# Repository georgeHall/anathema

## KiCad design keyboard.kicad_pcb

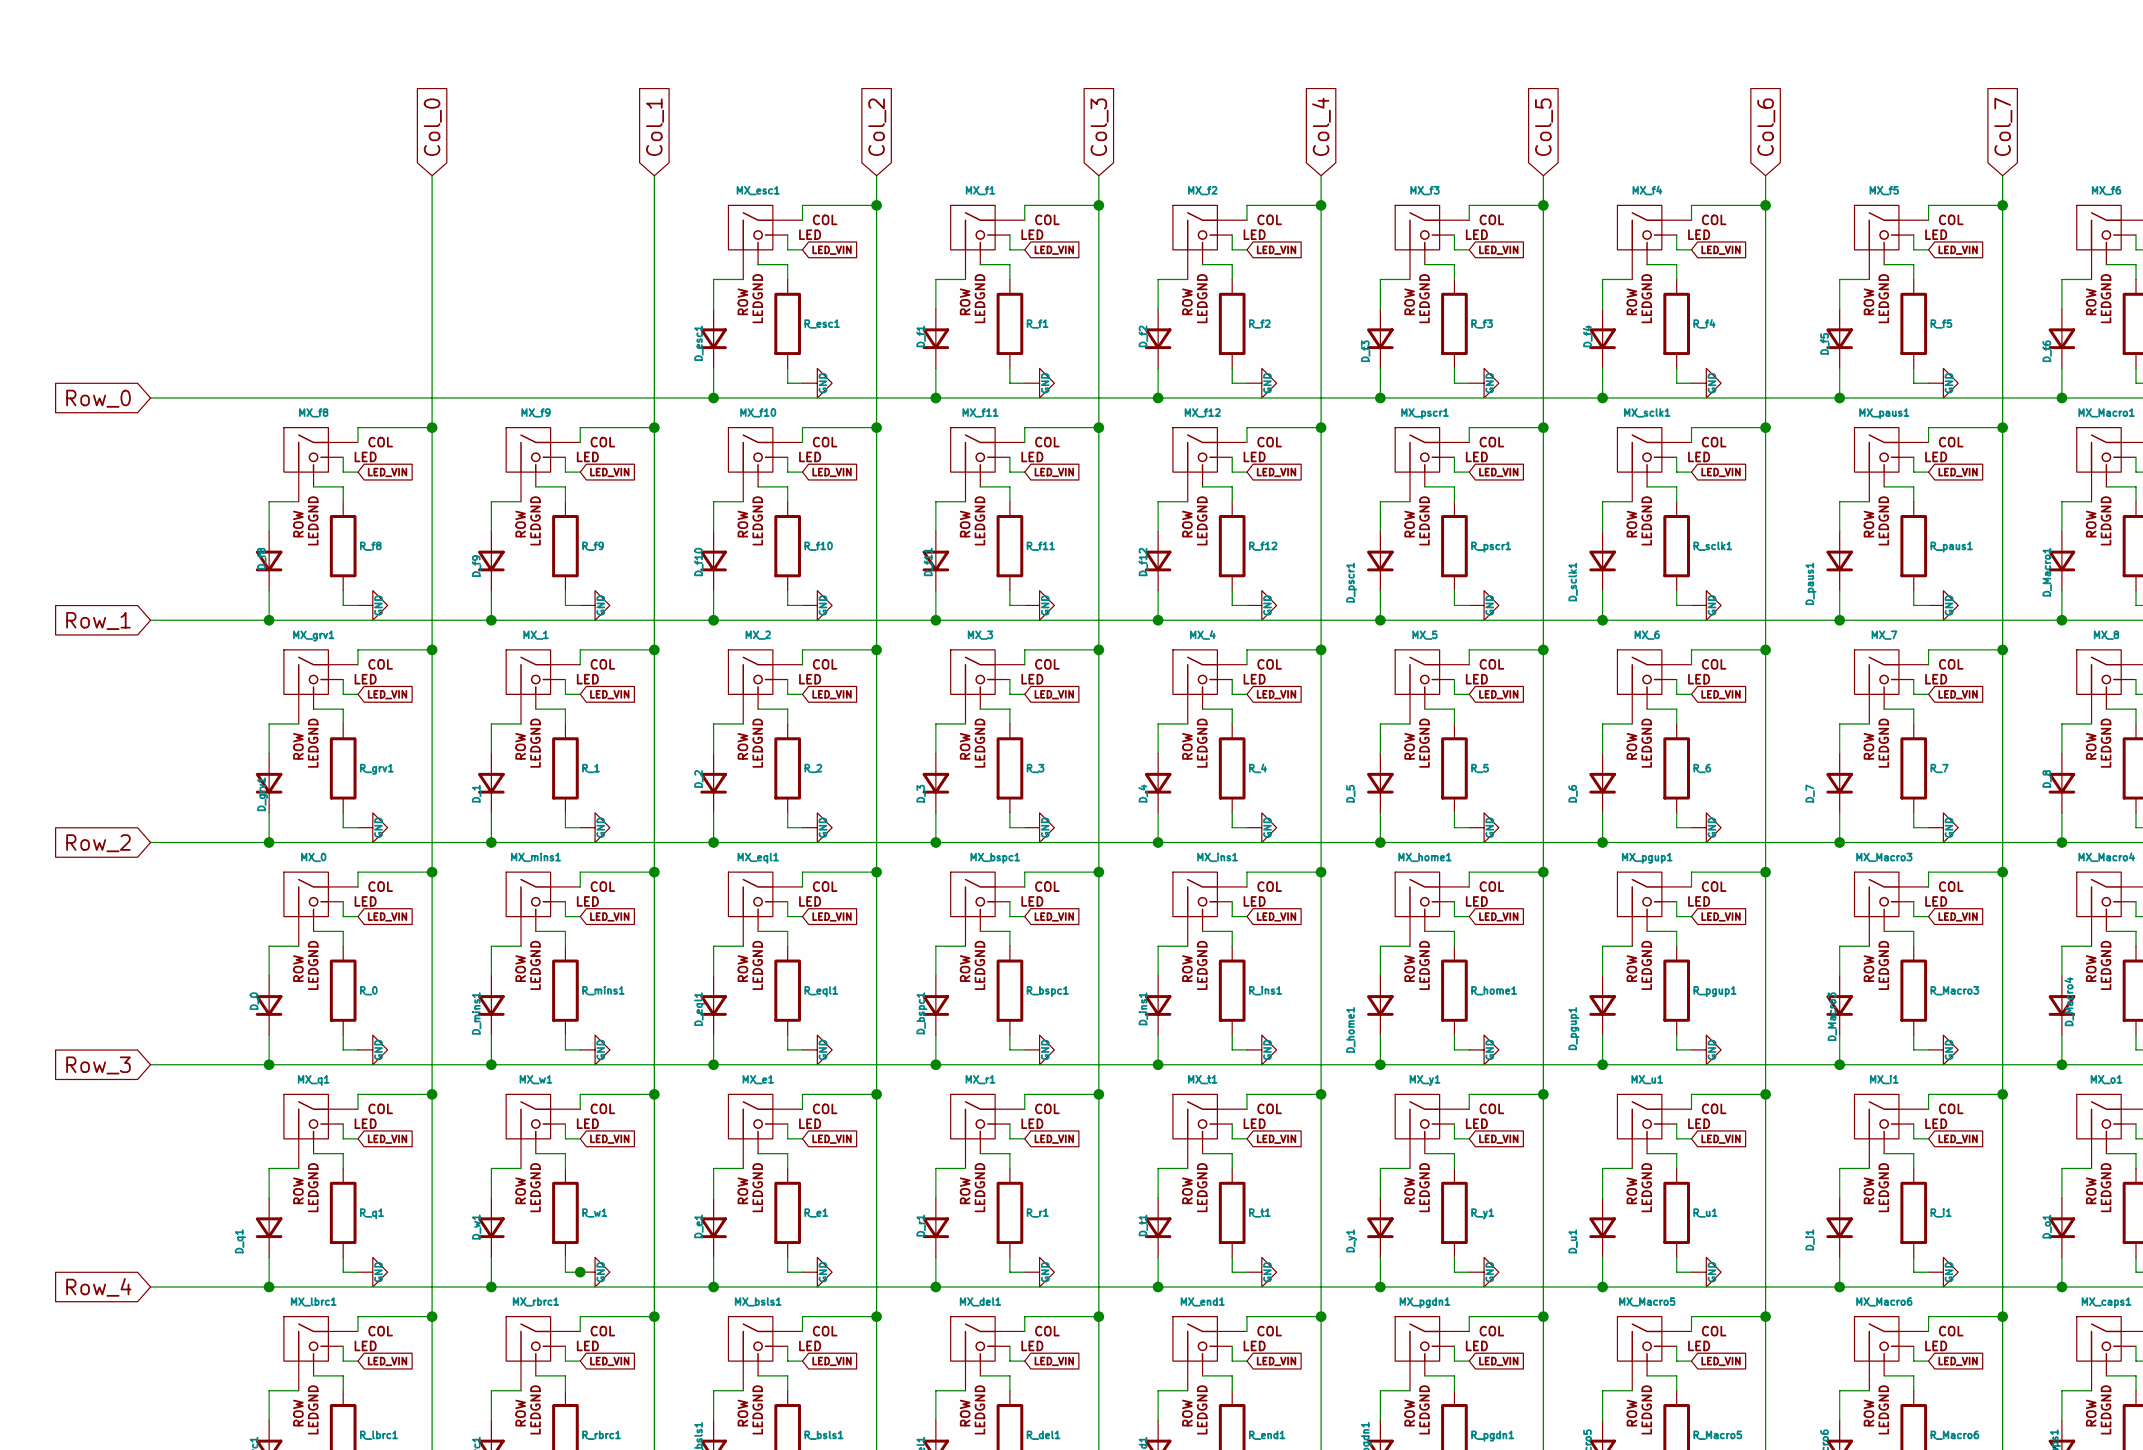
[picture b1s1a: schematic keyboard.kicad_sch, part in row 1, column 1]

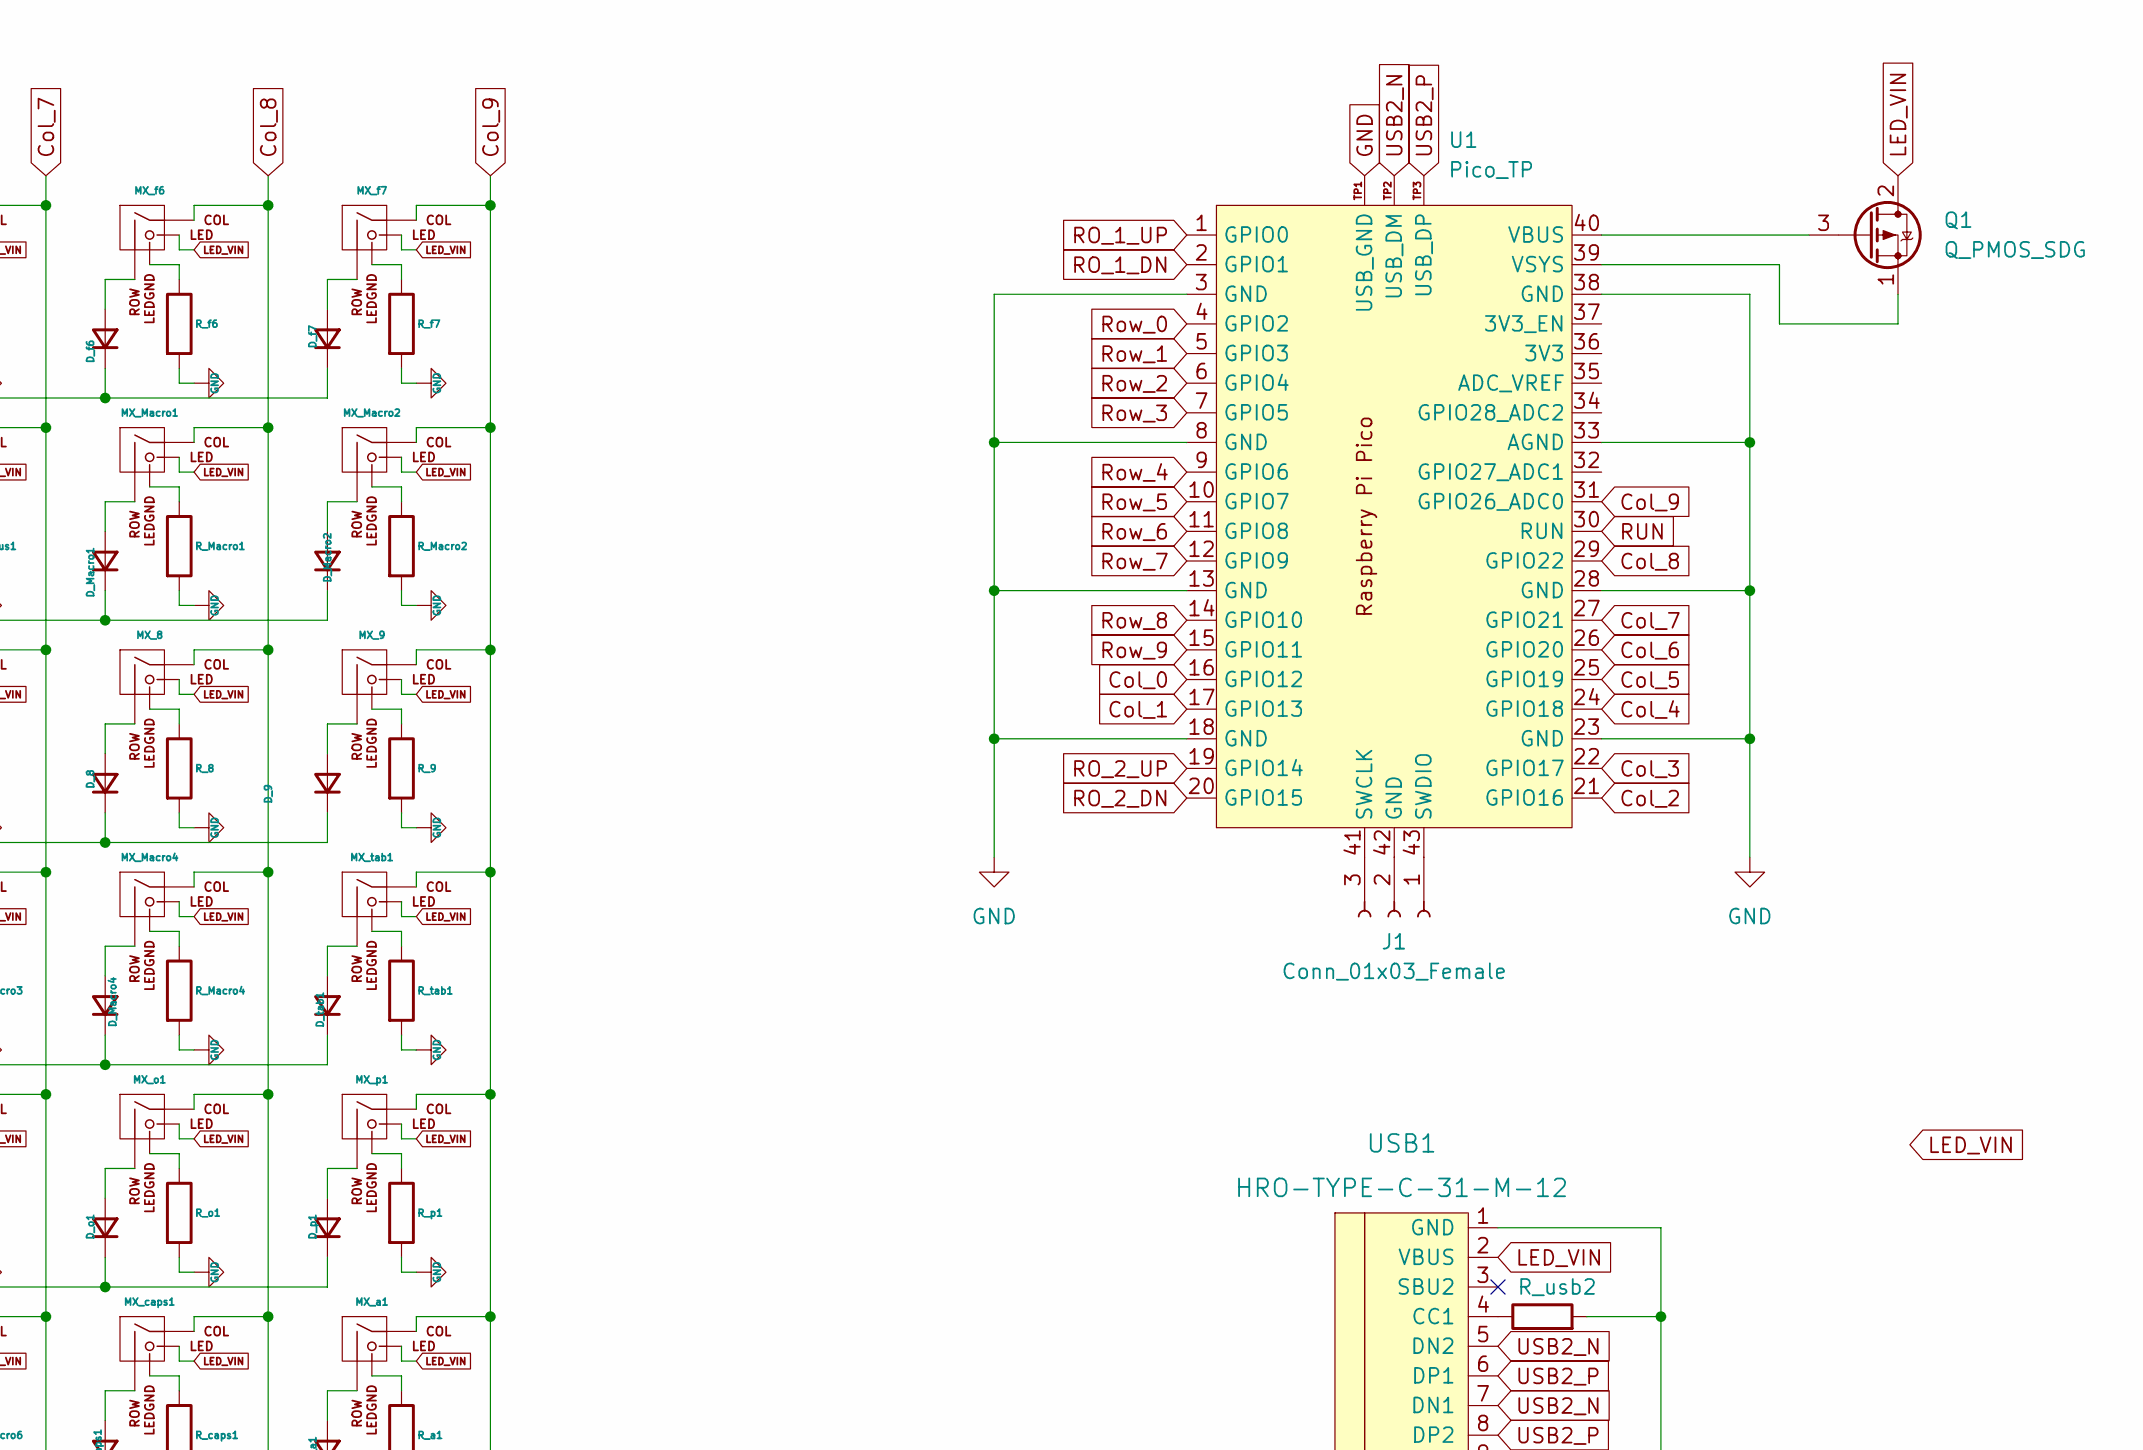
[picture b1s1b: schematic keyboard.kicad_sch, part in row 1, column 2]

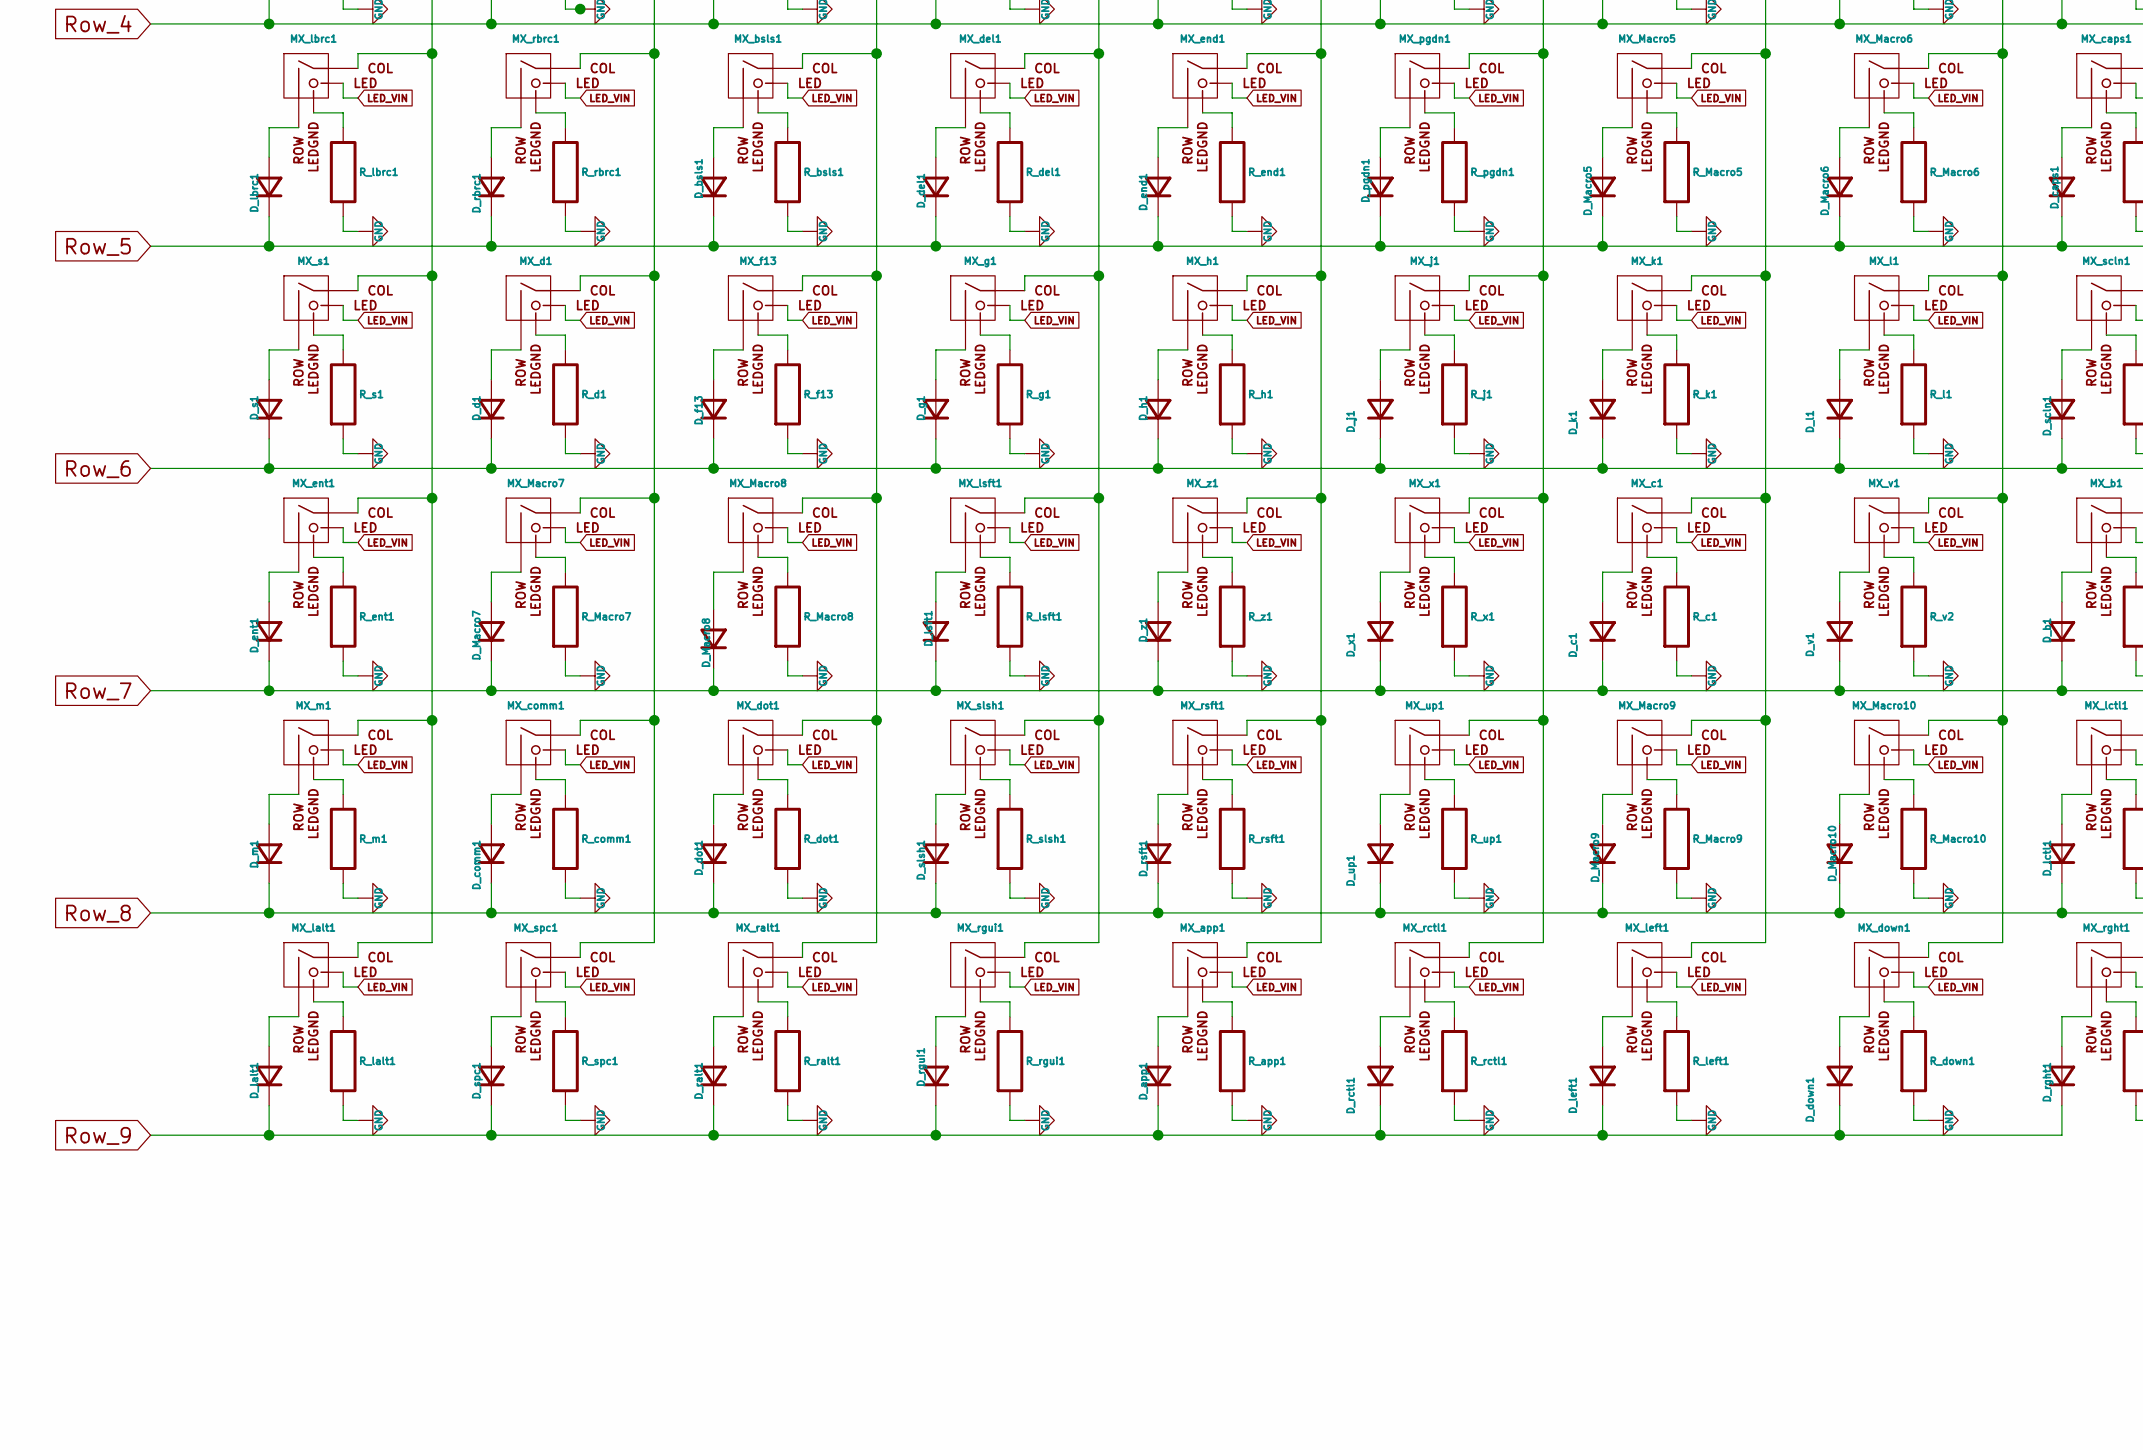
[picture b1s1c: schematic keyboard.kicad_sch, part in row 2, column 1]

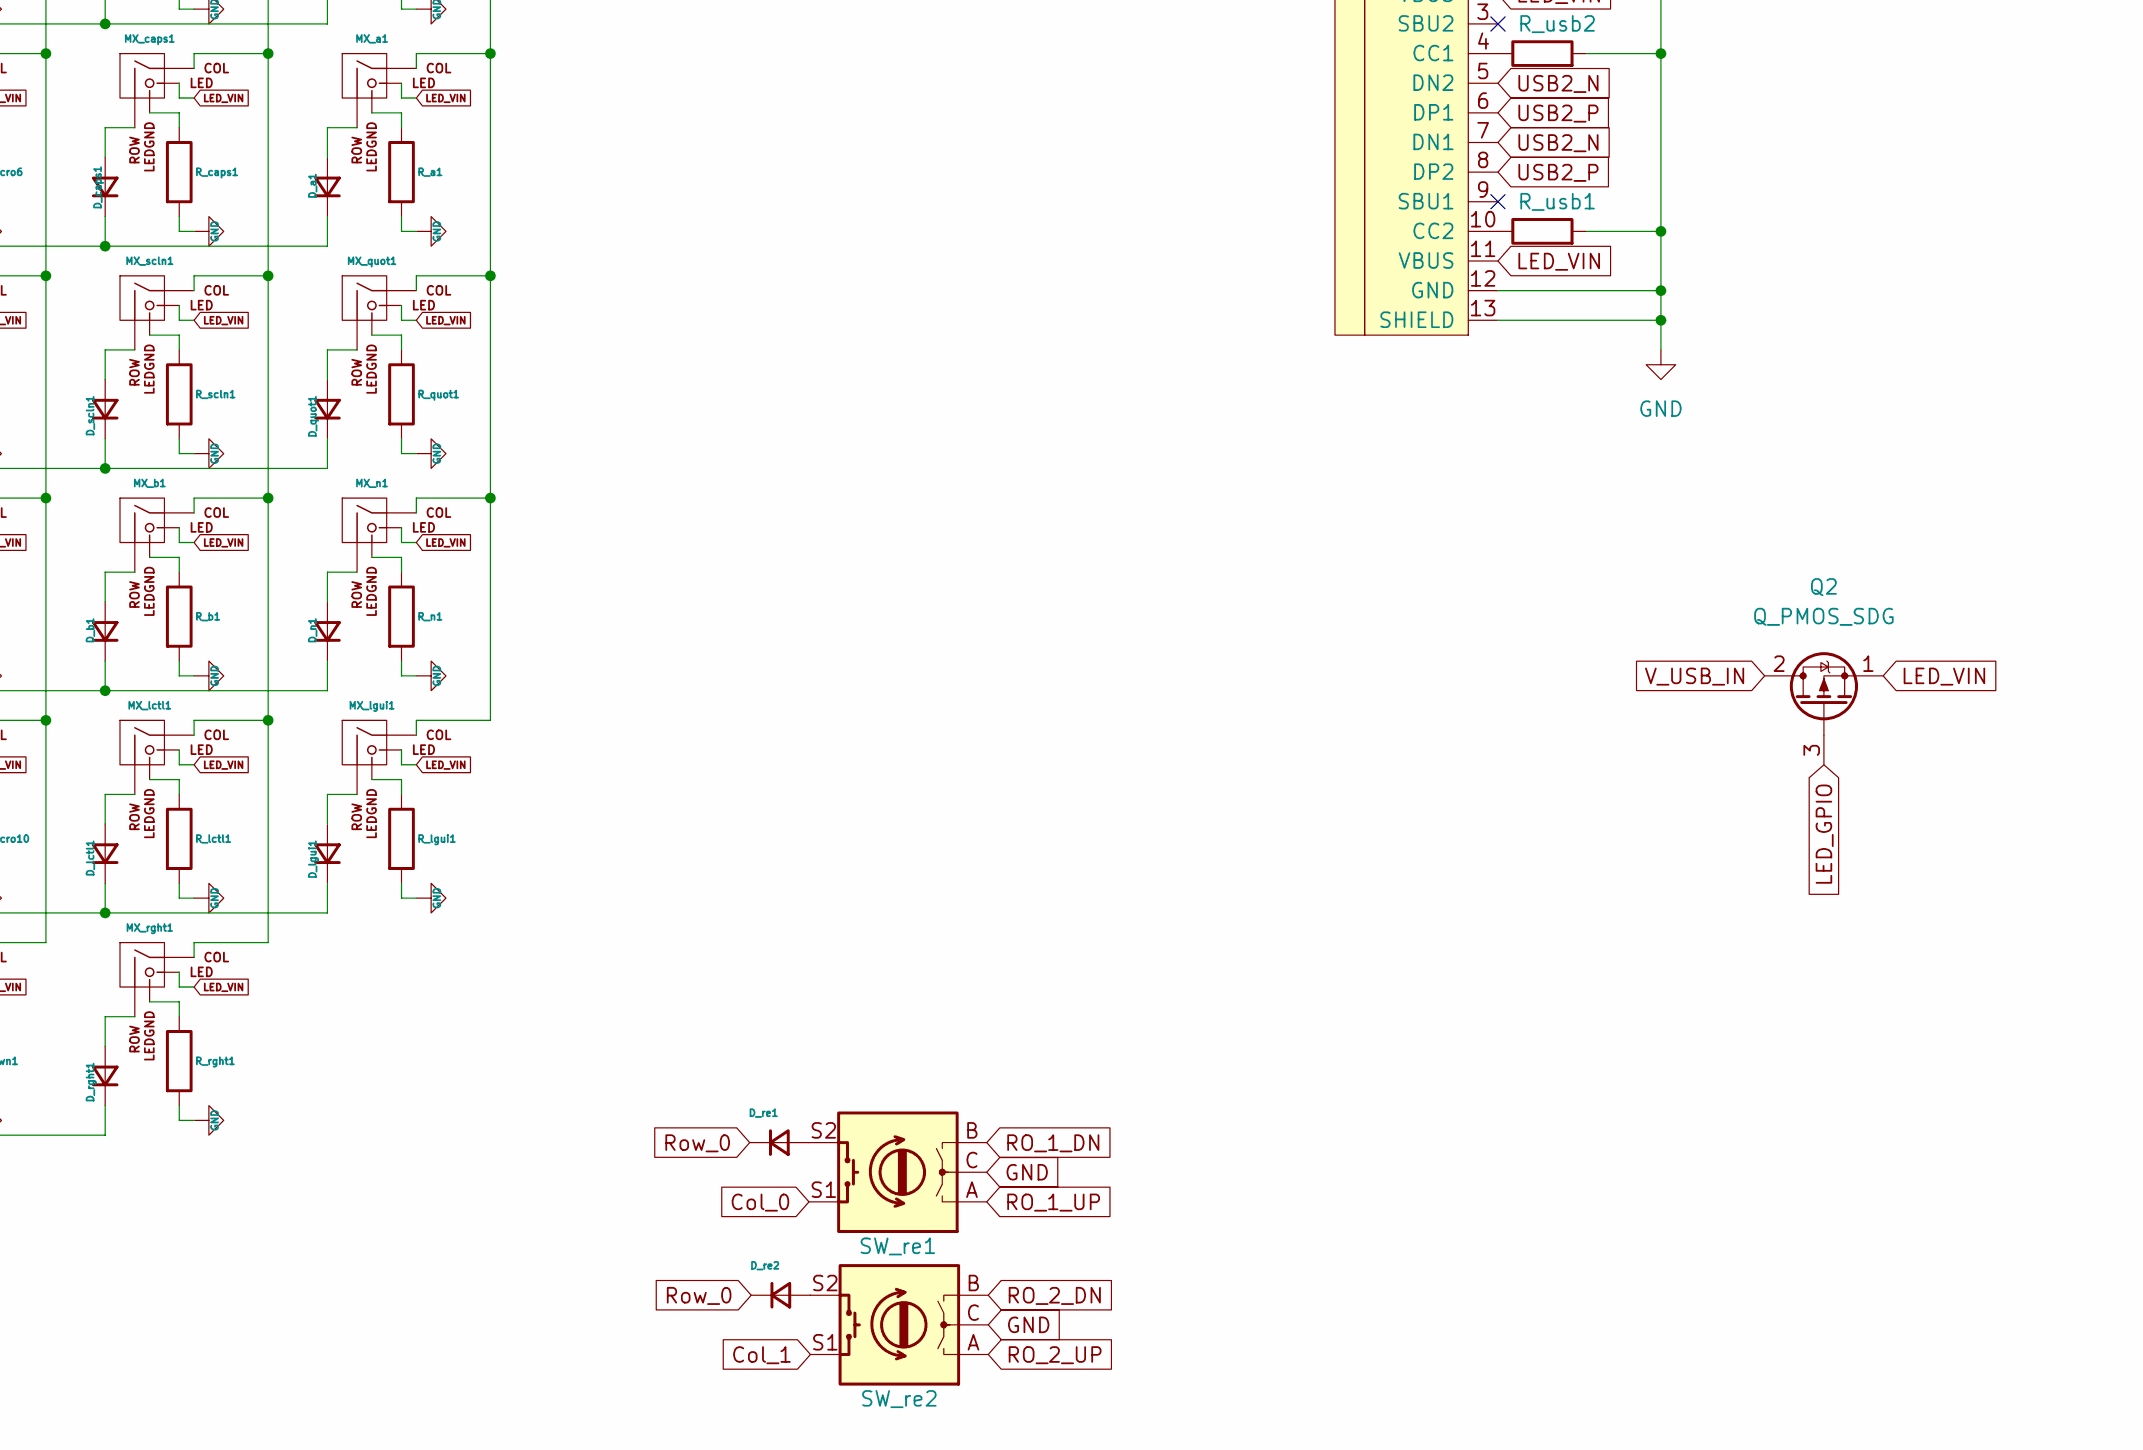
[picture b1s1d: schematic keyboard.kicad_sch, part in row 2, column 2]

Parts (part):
D_0, D_1, D_2, D_3, D_4, D_5, D_6, D_7, D_8, D_9: D_Small; D_0805_2012Metric_Pad1.15x1.40mm_HandSolder
D_Macro1, D_Macro2, D_Macro3, D_Macro4, D_Macro5, D_Macro6, D_Macro7, D_Macro8, D_Macro9, D_Macro10: D_Small; D_0805_2012Metric_Pad1.15x1.40mm_HandSolder
D_a1: D_Small; D_0805_2012Metric_Pad1.15x1.40mm_HandSolder
D_app1: D_Small; D_0805_2012Metric_Pad1.15x1.40mm_HandSolder
D_b1: D_Small; D_0805_2012Metric_Pad1.15x1.40mm_HandSolder
D_bsls1: D_Small; D_0805_2012Metric_Pad1.15x1.40mm_HandSolder
D_bspc1: D_Small; D_0805_2012Metric_Pad1.15x1.40mm_HandSolder
D_c1: D_Small; D_0805_2012Metric_Pad1.15x1.40mm_HandSolder
D_caps1: D_Small; D_0805_2012Metric_Pad1.15x1.40mm_HandSolder
D_comm1: D_Small; D_0805_2012Metric_Pad1.15x1.40mm_HandSolder
D_d1: D_Small; D_0805_2012Metric_Pad1.15x1.40mm_HandSolder
D_del1: D_Small; D_0805_2012Metric_Pad1.15x1.40mm_HandSolder
D_dot1: D_Small; D_0805_2012Metric_Pad1.15x1.40mm_HandSolder
D_down1: D_Small; D_0805_2012Metric_Pad1.15x1.40mm_HandSolder
D_e1: D_Small; D_0805_2012Metric_Pad1.15x1.40mm_HandSolder
D_end1: D_Small; D_0805_2012Metric_Pad1.15x1.40mm_HandSolder
D_ent1: D_Small; D_0805_2012Metric_Pad1.15x1.40mm_HandSolder
D_eql1: D_Small; D_0805_2012Metric_Pad1.15x1.40mm_HandSolder
D_esc1: D_Small; D_0805_2012Metric_Pad1.15x1.40mm_HandSolder
D_f1, D_f2, D_f3, D_f4, D_f5, D_f6, D_f7, D_f8, D_f9, D_f10, D_f11, D_f12, D_f13: D_Small; D_0805_2012Metric_Pad1.15x1.40mm_HandSolder
D_g1: D_Small; D_0805_2012Metric_Pad1.15x1.40mm_HandSolder
D_grv1: D_Small; D_0805_2012Metric_Pad1.15x1.40mm_HandSolder
D_h1: D_Small; D_0805_2012Metric_Pad1.15x1.40mm_HandSolder
D_home1: D_Small; D_0805_2012Metric_Pad1.15x1.40mm_HandSolder
D_i1: D_Small; D_0805_2012Metric_Pad1.15x1.40mm_HandSolder
D_ins1: D_Small; D_0805_2012Metric_Pad1.15x1.40mm_HandSolder
D_j1: D_Small; D_0805_2012Metric_Pad1.15x1.40mm_HandSolder
D_k1: D_Small; D_0805_2012Metric_Pad1.15x1.40mm_HandSolder
D_l1: D_Small; D_0805_2012Metric_Pad1.15x1.40mm_HandSolder
D_lalt1: D_Small; D_0805_2012Metric_Pad1.15x1.40mm_HandSolder
D_lbrc1: D_Small; D_0805_2012Metric_Pad1.15x1.40mm_HandSolder
D_lctl1: D_Small; D_0805_2012Metric_Pad1.15x1.40mm_HandSolder
D_left1: D_Small; D_0805_2012Metric_Pad1.15x1.40mm_HandSolder
D_lgui1: D_Small; D_0805_2012Metric_Pad1.15x1.40mm_HandSolder
D_lsft1: D_Small; D_0805_2012Metric_Pad1.15x1.40mm_HandSolder
D_m1: D_Small; D_0805_2012Metric_Pad1.15x1.40mm_HandSolder
D_mins1: D_Small; D_0805_2012Metric_Pad1.15x1.40mm_HandSolder
D_n1: D_Small; D_0805_2012Metric_Pad1.15x1.40mm_HandSolder
D_o1: D_Small; D_0805_2012Metric_Pad1.15x1.40mm_HandSolder
D_p1: D_Small; D_0805_2012Metric_Pad1.15x1.40mm_HandSolder
D_paus1: D_Small; D_0805_2012Metric_Pad1.15x1.40mm_HandSolder
D_pgdn1: D_Small; D_0805_2012Metric_Pad1.15x1.40mm_HandSolder
D_pgup1: D_Small; D_0805_2012Metric_Pad1.15x1.40mm_HandSolder
D_pscr1: D_Small; D_0805_2012Metric_Pad1.15x1.40mm_HandSolder
D_q1: D_Small; D_0805_2012Metric_Pad1.15x1.40mm_HandSolder
D_quot1: D_Small; D_0805_2012Metric_Pad1.15x1.40mm_HandSolder
D_r1: D_Small; D_0805_2012Metric_Pad1.15x1.40mm_HandSolder
D_ralt1: D_Small; D_0805_2012Metric_Pad1.15x1.40mm_HandSolder
D_rbrc1: D_Small; D_0805_2012Metric_Pad1.15x1.40mm_HandSolder
D_rctl1: D_Small; D_0805_2012Metric_Pad1.15x1.40mm_HandSolder
D_re1, D_re2: D_Small; D_0805_2012Metric_Pad1.15x1.40mm_HandSolder
D_rght1: D_Small; D_0805_2012Metric_Pad1.15x1.40mm_HandSolder
D_rgui1: D_Small; D_0805_2012Metric_Pad1.15x1.40mm_HandSolder
D_rsft1: D_Small; D_0805_2012Metric_Pad1.15x1.40mm_HandSolder
D_s1: D_Small; D_0805_2012Metric_Pad1.15x1.40mm_HandSolder
D_sclk1: D_Small; D_0805_2012Metric_Pad1.15x1.40mm_HandSolder
D_scln1: D_Small; D_0805_2012Metric_Pad1.15x1.40mm_HandSolder
D_slsh1: D_Small; D_0805_2012Metric_Pad1.15x1.40mm_HandSolder
D_spc1: D_Small; D_0805_2012Metric_Pad1.15x1.40mm_HandSolder
D_t1: D_Small; D_0805_2012Metric_Pad1.15x1.40mm_HandSolder
D_tab1: D_Small; D_0805_2012Metric_Pad1.15x1.40mm_HandSolder
D_u1: D_Small; D_0805_2012Metric_Pad1.15x1.40mm_HandSolder
D_up1: D_Small; D_0805_2012Metric_Pad1.15x1.40mm_HandSolder
D_v1: D_Small; D_0805_2012Metric_Pad1.15x1.40mm_HandSolder
D_w1: D_Small; D_0805_2012Metric_Pad1.15x1.40mm_HandSolder
D_x1: D_Small; D_0805_2012Metric_Pad1.15x1.40mm_HandSolder
D_y1: D_Small; D_0805_2012Metric_Pad1.15x1.40mm_HandSolder
D_z1: D_Small; D_0805_2012Metric_Pad1.15x1.40mm_HandSolder
J1: Conn_01x03_Female
MX_0, MX_1, MX_2, MX_3, MX_4, MX_5, MX_6, MX_7, MX_8, MX_9: MX-LED; MXOnly-1U
MX_Macro1, MX_Macro2, MX_Macro3, MX_Macro4, MX_Macro5, MX_Macro6, MX_Macro7, MX_Macro8, MX_Macro9, MX_Macro10: MX-LED; MXOnly-1U
MX_a1: MX-LED; MXOnly-1U
MX_app1: MX-LED; MXOnly-1.25U
MX_b1: MX-LED; MXOnly-1U
MX_bsls1: MX-LED; MXOnly-1.5U
MX_bspc1: MX-LED; MXOnly-2U
MX_c1: MX-LED; MXOnly-1U
MX_caps1: MX-LED; MXOnly-1.75U
MX_comm1: MX-LED; MXOnly-1U
MX_d1: MX-LED; MXOnly-1U
MX_del1: MX-LED; MXOnly-1U
MX_dot1: MX-LED; MXOnly-1U
MX_down1: MX-LED; MXOnly-1U
MX_e1: MX-LED; MXOnly-1U
MX_end1: MX-LED; MXOnly-1U
MX_ent1: MX-LED; MXOnly-2.25U
MX_eql1: MX-LED; MXOnly-1U
MX_esc1: MX-LED; MXOnly-1U
MX_f1, MX_f2, MX_f3, MX_f4, MX_f5, MX_f6, MX_f7, MX_f8, MX_f9, MX_f10, MX_f11, MX_f12, MX_f13: MX-LED; MXOnly-1U
MX_g1: MX-LED; MXOnly-1U
MX_grv1: MX-LED; MXOnly-1U
MX_h1: MX-LED; MXOnly-1U
MX_home1: MX-LED; MXOnly-1U
MX_i1: MX-LED; MXOnly-1U
MX_ins1: MX-LED; MXOnly-1U
MX_j1: MX-LED; MXOnly-1U
MX_k1: MX-LED; MXOnly-1U
MX_l1: MX-LED; MXOnly-1U
MX_lalt1: MX-LED; MXOnly-1.25U
MX_lbrc1: MX-LED; MXOnly-1U
MX_lctl1: MX-LED; MXOnly-1.25U
MX_left1: MX-LED; MXOnly-1U
MX_lgui1: MX-LED; MXOnly-1.25U
MX_lsft1: MX-LED; MXOnly-2.25U
MX_m1: MX-LED; MXOnly-1U
MX_mins1: MX-LED; MXOnly-1U
MX_n1: MX-LED; MXOnly-1U
MX_o1: MX-LED; MXOnly-1U
MX_p1: MX-LED; MXOnly-1U
MX_paus1: MX-LED; MXOnly-1U
MX_pgdn1: MX-LED; MXOnly-1U
MX_pgup1: MX-LED; MXOnly-1U
MX_pscr1: MX-LED; MXOnly-1U
MX_q1: MX-LED; MXOnly-1U
MX_quot1: MX-LED; MXOnly-1U
MX_r1: MX-LED; MXOnly-1U
MX_ralt1: MX-LED; MXOnly-1.25U
MX_rbrc1: MX-LED; MXOnly-1U
MX_rctl1: MX-LED; MXOnly-1.25U
MX_rght1: MX-LED; MXOnly-1U
MX_rgui1: MX-LED; MXOnly-1.25U
MX_rsft1: MX-LED; MXOnly-2.75U
MX_s1: MX-LED; MXOnly-1U
MX_sclk1: MX-LED; MXOnly-1U
MX_scln1: MX-LED; MXOnly-1U
MX_slsh1: MX-LED; MXOnly-1U
MX_spc1: MX-LED; MXOnly-6.25U-ReversedStabilizers
MX_t1: MX-LED; MXOnly-1U
MX_tab1: MX-LED; MXOnly-1.5U
MX_u1: MX-LED; MXOnly-1U
MX_up1: MX-LED; MXOnly-1U
MX_v1: MX-LED; MXOnly-1U
MX_w1: MX-LED; MXOnly-1U
MX_x1: MX-LED; MXOnly-1U
MX_y1: MX-LED; MXOnly-1U
MX_z1: MX-LED; MXOnly-1U
Q1, Q2: Q_PMOS_SDG
R_0, R_1, R_2, R_3, R_4, R_5, R_6, R_7, R_8, R_9: R; R_0805_2012Metric_Pad1.20x1.40mm_HandSolder
R_Macro1, R_Macro2, R_Macro3, R_Macro4, R_Macro5, R_Macro6, R_Macro7, R_Macro8, R_Macro9, R_Macro10: R; R_0805_2012Metric_Pad1.20x1.40mm_HandSolder
R_a1: R; R_0805_2012Metric_Pad1.20x1.40mm_HandSolder
R_app1: R; R_0805_2012Metric_Pad1.20x1.40mm_HandSolder
R_b1: R; R_0805_2012Metric_Pad1.20x1.40mm_HandSolder
R_bsls1: R; R_0805_2012Metric_Pad1.20x1.40mm_HandSolder
R_bspc1: R; R_0805_2012Metric_Pad1.20x1.40mm_HandSolder
R_c1: R; R_0805_2012Metric_Pad1.20x1.40mm_HandSolder
R_caps1: R; R_0805_2012Metric_Pad1.20x1.40mm_HandSolder
R_comm1: R; R_0805_2012Metric_Pad1.20x1.40mm_HandSolder
R_d1: R; R_0805_2012Metric_Pad1.20x1.40mm_HandSolder
R_del1: R; R_0805_2012Metric_Pad1.20x1.40mm_HandSolder
R_dot1: R; R_0805_2012Metric_Pad1.20x1.40mm_HandSolder
R_down1: R; R_0805_2012Metric_Pad1.20x1.40mm_HandSolder
R_e1: R; R_0805_2012Metric_Pad1.20x1.40mm_HandSolder
R_end1: R; R_0805_2012Metric_Pad1.20x1.40mm_HandSolder
R_ent1: R; R_0805_2012Metric_Pad1.20x1.40mm_HandSolder
R_eql1: R; R_0805_2012Metric_Pad1.20x1.40mm_HandSolder
R_esc1: R; R_0805_2012Metric_Pad1.20x1.40mm_HandSolder
R_f1, R_f2, R_f3, R_f4, R_f5, R_f6, R_f7, R_f8, R_f9, R_f10, R_f11, R_f12, R_f13: R; R_0805_2012Metric_Pad1.20x1.40mm_HandSolder
R_g1: R; R_0805_2012Metric_Pad1.20x1.40mm_HandSolder
R_grv1: R; R_0805_2012Metric_Pad1.20x1.40mm_HandSolder
R_h1: R; R_0805_2012Metric_Pad1.20x1.40mm_HandSolder
R_home1: R; R_0805_2012Metric_Pad1.20x1.40mm_HandSolder
R_i1: R; R_0805_2012Metric_Pad1.20x1.40mm_HandSolder
R_ins1: R; R_0805_2012Metric_Pad1.20x1.40mm_HandSolder
R_j1: R; R_0805_2012Metric_Pad1.20x1.40mm_HandSolder
R_k1: R; R_0805_2012Metric_Pad1.20x1.40mm_HandSolder
R_l1: R; R_0805_2012Metric_Pad1.20x1.40mm_HandSolder
R_lalt1: R; R_0805_2012Metric_Pad1.20x1.40mm_HandSolder
R_lbrc1: R; R_0805_2012Metric_Pad1.20x1.40mm_HandSolder
R_lctl1: R; R_0805_2012Metric_Pad1.20x1.40mm_HandSolder
R_left1: R; R_0805_2012Metric_Pad1.20x1.40mm_HandSolder
R_lgui1: R; R_0805_2012Metric_Pad1.20x1.40mm_HandSolder
R_lsft1: R; R_0805_2012Metric_Pad1.20x1.40mm_HandSolder
R_m1: R; R_0805_2012Metric_Pad1.20x1.40mm_HandSolder
R_mins1: R; R_0805_2012Metric_Pad1.20x1.40mm_HandSolder
R_n1: R; R_0805_2012Metric_Pad1.20x1.40mm_HandSolder
R_o1: R; R_0805_2012Metric_Pad1.20x1.40mm_HandSolder
R_p1: R; R_0805_2012Metric_Pad1.20x1.40mm_HandSolder
R_paus1: R; R_0805_2012Metric_Pad1.20x1.40mm_HandSolder
R_pgdn1: R; R_0805_2012Metric_Pad1.20x1.40mm_HandSolder
R_pgup1: R; R_0805_2012Metric_Pad1.20x1.40mm_HandSolder
R_pscr1: R; R_0805_2012Metric_Pad1.20x1.40mm_HandSolder
R_q1: R; R_0805_2012Metric_Pad1.20x1.40mm_HandSolder
R_quot1: R; R_0805_2012Metric_Pad1.20x1.40mm_HandSolder
R_r1: R; R_0805_2012Metric_Pad1.20x1.40mm_HandSolder
R_ralt1: R; R_0805_2012Metric_Pad1.20x1.40mm_HandSolder
R_rbrc1: R; R_0805_2012Metric_Pad1.20x1.40mm_HandSolder
R_rctl1: R; R_0805_2012Metric_Pad1.20x1.40mm_HandSolder
R_rght1: R; R_0805_2012Metric_Pad1.20x1.40mm_HandSolder
R_rgui1: R; R_0805_2012Metric_Pad1.20x1.40mm_HandSolder
R_rsft1: R; R_0805_2012Metric_Pad1.20x1.40mm_HandSolder
R_s1: R; R_0805_2012Metric_Pad1.20x1.40mm_HandSolder
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
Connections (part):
Col_0: MX_0.1 (COL), MX_ent1.1 (COL), MX_f8.1 (COL), MX_grv1.1 (COL), MX_lalt1.1 (COL), MX_lbrc1.1 (COL), MX_m1.1 (COL), MX_q1.1 (COL), MX_s1.1 (COL), SW_re1.S1, U1.16 (GPIO12)
Col_1: MX_1.1 (COL), MX_Macro7.1 (COL), MX_comm1.1 (COL), MX_d1.1 (COL), MX_f9.1 (COL), MX_mins1.1 (COL), MX_rbrc1.1 (COL), MX_spc1.1 (COL), MX_w1.1 (COL), SW_re2.S1, U1.17 (GPIO13)
Col_2: MX_2.1 (COL), MX_Macro8.1 (COL), MX_bsls1.1 (COL), MX_dot1.1 (COL), MX_e1.1 (COL), MX_eql1.1 (COL), MX_esc1.1 (COL), MX_f10.1 (COL), MX_f13.1 (COL), MX_ralt1.1 (COL), U1.21 (GPIO16)
Col_3: MX_3.1 (COL), MX_bspc1.1 (COL), MX_del1.1 (COL), MX_f1.1 (COL), MX_f11.1 (COL), MX_g1.1 (COL), MX_lsft1.1 (COL), MX_r1.1 (COL), MX_rgui1.1 (COL), MX_slsh1.1 (COL), U1.22 (GPIO17)
Col_4: MX_4.1 (COL), MX_app1.1 (COL), MX_end1.1 (COL), MX_f2.1 (COL), MX_f12.1 (COL), MX_h1.1 (COL), MX_ins1.1 (COL), MX_rsft1.1 (COL), MX_t1.1 (COL), MX_z1.1 (COL), U1.24 (GPIO18)
Col_5: MX_5.1 (COL), MX_f3.1 (COL), MX_home1.1 (COL), MX_j1.1 (COL), MX_pgdn1.1 (COL), MX_pscr1.1 (COL), MX_rctl1.1 (COL), MX_up1.1 (COL), MX_x1.1 (COL), MX_y1.1 (COL), U1.25 (GPIO19)
Col_6: MX_6.1 (COL), MX_Macro5.1 (COL), MX_Macro9.1 (COL), MX_c1.1 (COL), MX_f4.1 (COL), MX_k1.1 (COL), MX_left1.1 (COL), MX_pgup1.1 (COL), MX_sclk1.1 (COL), MX_u1.1 (COL), U1.26 (GPIO20)
Col_7: MX_7.1 (COL), MX_Macro3.1 (COL), MX_Macro6.1 (COL), MX_Macro10.1 (COL), MX_down1.1 (COL), MX_f5.1 (COL), MX_i1.1 (COL), MX_l1.1 (COL), MX_paus1.1 (COL), MX_v1.1 (COL), U1.27 (GPIO21)
Col_8: MX_8.1 (COL), MX_Macro1.1 (COL), MX_Macro4.1 (COL), MX_b1.1 (COL), MX_caps1.1 (COL), MX_f6.1 (COL), MX_lctl1.1 (COL), MX_o1.1 (COL), MX_rght1.1 (COL), MX_scln1.1 (COL), U1.29 (GPIO22)
Col_9: MX_9.1 (COL), MX_Macro2.1 (COL), MX_a1.1 (COL), MX_f7.1 (COL), MX_lgui1.1 (COL), MX_n1.1 (COL), MX_p1.1 (COL), MX_quot1.1 (COL), MX_tab1.1 (COL), U1.31 (GPIO26_ADC0)
GND: R_0.2, R_1.2, R_2.2, R_3.2, R_4.2, R_5.2, R_6.2, R_7.2, R_8.2, R_9.2, R_Macro1.2, R_Macro2.2, R_Macro3.2, R_Macro4.2, R_Macro5.2, R_Macro6.2, R_Macro7.2, R_Macro8.2, R_Macro9.2, R_Macro10.2, R_a1.2, R_app1.2, R_b1.2, R_bsls1.2, R_bspc1.2, R_c1.2, R_caps1.2, R_comm1.2, R_d1.2, R_del1.2, R_dot1.2, R_down1.2, R_e1.2, R_end1.2, R_ent1.2, R_eql1.2, R_esc1.2, R_f1.2, R_f2.2, R_f3.2, R_f4.2, R_f5.2, R_f6.2, R_f7.2, R_f8.2, R_f9.2, R_f10.2, R_f11.2, R_f12.2, R_f13.2, R_g1.2, R_grv1.2, R_h1.2, R_home1.2, R_i1.2, R_ins1.2, R_j1.2, R_k1.2, R_l1.2, R_lalt1.2, R_lbrc1.2, R_lctl1.2, R_left1.2, R_lgui1.2, R_lsft1.2, R_m1.2, R_mins1.2, R_n1.2, R_o1.2, R_p1.2, R_paus1.2, R_pgdn1.2, R_pgup1.2, R_pscr1.2, R_q1.2, R_quot1.2, R_r1.2, R_ralt1.2, R_rbrc1.2, R_rctl1.2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
LED_VIN: MX_0.3 (LED), MX_1.3 (LED), MX_2.3 (LED), MX_3.3 (LED), MX_4.3 (LED), MX_5.3 (LED), MX_6.3 (LED), MX_7.3 (LED), MX_8.3 (LED), MX_9.3 (LED), MX_Macro1.3 (LED), MX_Macro2.3 (LED), MX_Macro3.3 (LED), MX_Macro4.3 (LED), MX_Macro5.3 (LED), MX_Macro6.3 (LED), MX_Macro7.3 (LED), MX_Macro8.3 (LED), MX_Macro9.3 (LED), MX_Macro10.3 (LED), MX_a1.3 (LED), MX_app1.3 (LED), MX_b1.3 (LED), MX_bsls1.3 (LED), MX_bspc1.3 (LED), MX_c1.3 (LED), MX_caps1.3 (LED), MX_comm1.3 (LED), MX_d1.3 (LED), MX_del1.3 (LED), MX_dot1.3 (LED), MX_down1.3 (LED), MX_e1.3 (LED), MX_end1.3 (LED), MX_ent1.3 (LED), MX_eql1.3 (LED), MX_esc1.3 (LED), MX_f1.3 (LED), MX_f2.3 (LED), MX_f3.3 (LED), MX_f4.3 (LED), MX_f5.3 (LED), MX_f6.3 (LED), MX_f7.3 (LED), MX_f8.3 (LED), MX_f9.3 (LED), MX_f10.3 (LED), MX_f11.3 (LED), MX_f12.3 (LED), MX_f13.3 (LED), MX_g1.3 (LED), MX_grv1.3 (LED), MX_h1.3 (LED), MX_home1.3 (LED), MX_i1.3 (LED), MX_ins1.3 (LED), MX_j1.3 (LED), MX_k1.3 (LED), MX_l1.3 (LED), MX_lalt1.3 (LED), MX_lbrc1.3 (LED), MX_lctl1.3 (LED), MX_left1.3 (LED), MX_lgui1.3 (LED), MX_lsft1.3 (LED), MX_m1.3 (LED), MX_mins1.3 (LED), MX_n1.3 (LED), MX_o1.3 (LED), MX_p1.3 (LED), MX_paus1.3 (LED), MX_pgdn1.3 (LED), MX_pgup1.3 (LED), MX_pscr1.3 (LED), MX_q1.3 (LED), MX_quot1.3 (LED), MX_r1.3 (LED), MX_ralt1.3 (LED), MX_rbrc1.3 (LED), MX_rctl1.3 (LED)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
unnamed: D_0.2 (A), MX_0.2 (ROW)
unnamed: D_1.2 (A), MX_1.2 (ROW)
unnamed: D_2.2 (A), MX_2.2 (ROW)
unnamed: D_3.2 (A), MX_3.2 (ROW)
unnamed: D_4.2 (A), MX_4.2 (ROW)
unnamed: D_5.2 (A), MX_5.2 (ROW)
unnamed: D_6.2 (A), MX_6.2 (ROW)
unnamed: D_7.2 (A), MX_7.2 (ROW)
unnamed: D_8.2 (A), MX_8.2 (ROW)
unnamed: D_9.2 (A), MX_9.2 (ROW)
unnamed: D_Macro1.2 (A), MX_Macro1.2 (ROW)
unnamed: D_Macro2.2 (A), MX_Macro2.2 (ROW)
unnamed: D_Macro3.2 (A), MX_Macro3.2 (ROW)
unnamed: D_Macro4.2 (A), MX_Macro4.2 (ROW)
unnamed: D_Macro5.2 (A), MX_Macro5.2 (ROW)
unnamed: D_Macro6.2 (A), MX_Macro6.2 (ROW)
unnamed: D_Macro7.2 (A), MX_Macro7.2 (ROW)
unnamed: D_Macro8.2 (A), MX_Macro8.2 (ROW)
unnamed: D_Macro9.2 (A), MX_Macro9.2 (ROW)
unnamed: D_Macro10.2 (A), MX_Macro10.2 (ROW)
unnamed: D_a1.2 (A), MX_a1.2 (ROW)
unnamed: D_app1.2 (A), MX_app1.2 (ROW)
unnamed: D_b1.2 (A), MX_b1.2 (ROW)
unnamed: D_bsls1.2 (A), MX_bsls1.2 (ROW)
unnamed: D_bspc1.2 (A), MX_bspc1.2 (ROW)
unnamed: D_c1.2 (A), MX_c1.2 (ROW)
unnamed: D_caps1.2 (A), MX_caps1.2 (ROW)
unnamed: D_comm1.2 (A), MX_comm1.2 (ROW)
unnamed: D_d1.2 (A), MX_d1.2 (ROW)
unnamed: D_del1.2 (A), MX_del1.2 (ROW)
unnamed: D_dot1.2 (A), MX_dot1.2 (ROW)
unnamed: D_down1.2 (A), MX_down1.2 (ROW)
unnamed: D_e1.2 (A), MX_e1.2 (ROW)
unnamed: D_end1.2 (A), MX_end1.2 (ROW)
unnamed: D_ent1.2 (A), MX_ent1.2 (ROW)
unnamed: D_eql1.2 (A), MX_eql1.2 (ROW)
unnamed: D_esc1.2 (A), MX_esc1.2 (ROW)
unnamed: D_f1.2 (A), MX_f1.2 (ROW)
unnamed: D_f2.2 (A), MX_f2.2 (ROW)
unnamed: D_f3.2 (A), MX_f3.2 (ROW)
unnamed: D_f4.2 (A), MX_f4.2 (ROW)
unnamed: D_f5.2 (A), MX_f5.2 (ROW)
unnamed: D_f6.2 (A), MX_f6.2 (ROW)
unnamed: D_f7.2 (A), MX_f7.2 (ROW)
unnamed: D_f8.2 (A), MX_f8.2 (ROW)
unnamed: D_f9.2 (A), MX_f9.2 (ROW)
unnamed: D_f10.2 (A), MX_f10.2 (ROW)
unnamed: D_f11.2 (A), MX_f11.2 (ROW)
unnamed: D_f12.2 (A), MX_f12.2 (ROW)
unnamed: D_f13.2 (A), MX_f13.2 (ROW)
unnamed: D_g1.2 (A), MX_g1.2 (ROW)
unnamed: D_grv1.2 (A), MX_grv1.2 (ROW)
unnamed: D_h1.2 (A), MX_h1.2 (ROW)
unnamed: D_home1.2 (A), MX_home1.2 (ROW)
unnamed: D_i1.2 (A), MX_i1.2 (ROW)
unnamed: D_ins1.2 (A), MX_ins1.2 (ROW)
unnamed: D_j1.2 (A), MX_j1.2 (ROW)
unnamed: D_k1.2 (A), MX_k1.2 (ROW)
unnamed: D_l1.2 (A), MX_l1.2 (ROW)
unnamed: D_lalt1.2 (A), MX_lalt1.2 (ROW)
unnamed: D_lbrc1.2 (A), MX_lbrc1.2 (ROW)
unnamed: D_lctl1.2 (A), MX_lctl1.2 (ROW)
unnamed: D_left1.2 (A), MX_left1.2 (ROW)
unnamed: D_lgui1.2 (A), MX_lgui1.2 (ROW)
unnamed: D_lsft1.2 (A), MX_lsft1.2 (ROW)
unnamed: D_m1.2 (A), MX_m1.2 (ROW)
unnamed: D_mins1.2 (A), MX_mins1.2 (ROW)
unnamed: D_n1.2 (A), MX_n1.2 (ROW)
unnamed: D_o1.2 (A), MX_o1.2 (ROW)
unnamed: D_p1.2 (A), MX_p1.2 (ROW)
unnamed: D_paus1.2 (A), MX_paus1.2 (ROW)
unnamed: D_pgdn1.2 (A), MX_pgdn1.2 (ROW)
unnamed: D_pgup1.2 (A), MX_pgup1.2 (ROW)
unnamed: D_pscr1.2 (A), MX_pscr1.2 (ROW)
unnamed: D_q1.2 (A), MX_q1.2 (ROW)
unnamed: D_quot1.2 (A), MX_quot1.2 (ROW)
unnamed: D_r1.2 (A), MX_r1.2 (ROW)
unnamed: D_ralt1.2 (A), MX_ralt1.2 (ROW)
unnamed: D_rbrc1.2 (A), MX_rbrc1.2 (ROW)
unnamed: D_rctl1.2 (A), MX_rctl1.2 (ROW)
unnamed: D_re1.2 (A), SW_re1.S2
unnamed: D_re2.2 (A), SW_re2.S2
unnamed: D_rght1.2 (A), MX_rght1.2 (ROW)
unnamed: D_rgui1.2 (A), MX_rgui1.2 (ROW)
unnamed: D_rsft1.2 (A), MX_rsft1.2 (ROW)
unnamed: D_s1.2 (A), MX_s1.2 (ROW)
unnamed: D_sclk1.2 (A), MX_sclk1.2 (ROW)
unnamed: D_scln1.2 (A), MX_scln1.2 (ROW)
unnamed: D_slsh1.2 (A), MX_slsh1.2 (ROW)
unnamed: D_spc1.2 (A), MX_spc1.2 (ROW)
unnamed: D_t1.2 (A), MX_t1.2 (ROW)
unnamed: D_tab1.2 (A), MX_tab1.2 (ROW)
unnamed: D_u1.2 (A), MX_u1.2 (ROW)
unnamed: D_up1.2 (A), MX_up1.2 (ROW)
unnamed: D_v1.2 (A), MX_v1.2 (ROW)
unnamed: D_w1.2 (A), MX_w1.2 (ROW)
unnamed: D_x1.2 (A), MX_x1.2 (ROW)
unnamed: D_y1.2 (A), MX_y1.2 (ROW)
unnamed: D_z1.2 (A), MX_z1.2 (ROW)
unnamed: J1.1, U1.43 (SWDIO)
unnamed: J1.2, U1.42 (GND)
unnamed: J1.3, U1.41 (SWCLK)
unnamed: MX_0.4 (LEDGND), R_0.1
unnamed: MX_1.4 (LEDGND), R_1.1
unnamed: MX_2.4 (LEDGND), R_2.1
unnamed: MX_3.4 (LEDGND), R_3.1
unnamed: MX_4.4 (LEDGND), R_4.1
unnamed: MX_5.4 (LEDGND), R_5.1
unnamed: MX_6.4 (LEDGND), R_6.1
unnamed: MX_7.4 (LEDGND), R_7.1
unnamed: MX_8.4 (LEDGND), R_8.1
unnamed: MX_9.4 (LEDGND), R_9.1
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
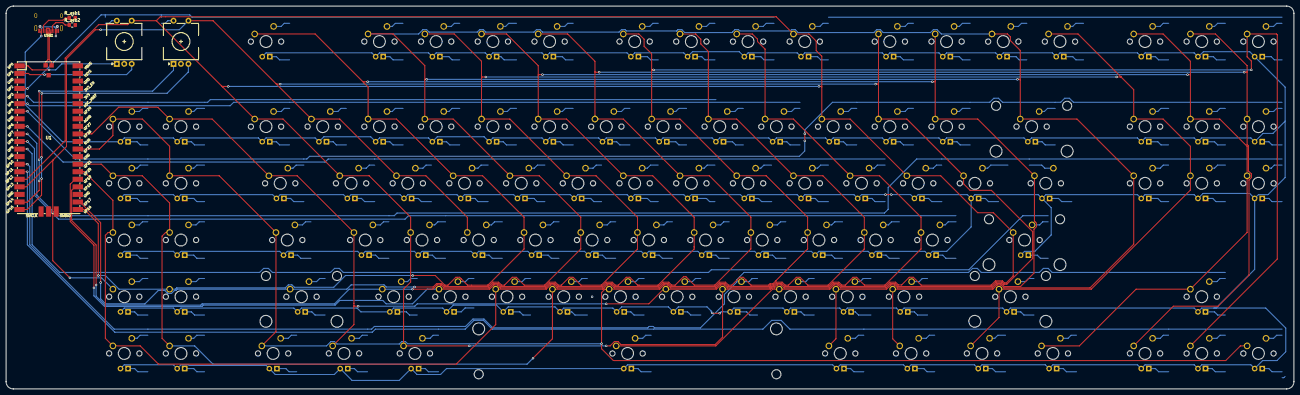
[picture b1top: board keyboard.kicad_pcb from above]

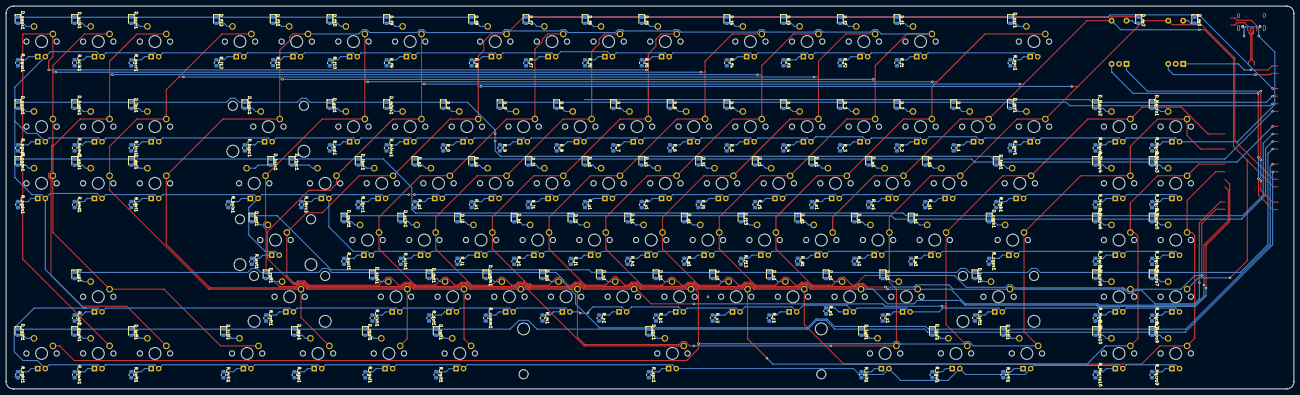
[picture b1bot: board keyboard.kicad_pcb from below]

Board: 2 copper layers, 432.6 x 128.6 mm, 299 parts (196 on the bottom side), 226 nets.

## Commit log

2022-08-31 Update to plan
2022-09-03 Keyboard
2022-09-05 Rev1
2022-09-05 rev 1
